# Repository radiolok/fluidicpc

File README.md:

# FluidicPC

Вычислительные устройства на элементах струйной логики: от моделей отдельных элементов и расчёта течения до синтеза схем и разводки плат.

## Проекты и инструменты

| Папка | Что внутри |
|---|---|
| [`calculator/`](calculator) | **Струйный калькулятор** — арт-объект на 852 элементах: распознаёт символ с матрицы трубочек 5 × 7, считает и показывает результат на семисегментных индикаторах. Модель, структурный и высокоуровневый Verilog, расчёты питания и конструктива |
| [`adder/`](adder) | 4-разрядный сумматор: Verilog, синтез в библиотеку струйных элементов (`fluidic.lib`), тестбенч |
| [`elements/`](elements) | 3D-модели элементов «Волга» (СТ41, СТ42, СТ43, СТ55, СТ56, СТ59, СТ60, СТ63 и др.) во FreeCAD |
| [`bench/`](bench) | расчёт течения в элементе СТ41 в OpenFOAM: подготовка сетки и запуск на кластере |
| [`sch/`](sch) | схемы и плата сумматора в KiCad |
| [`verilog2netlist/`](verilog2netlist) | конвертер синтезированного Verilog в netlist и плату KiCad |

## Струйный калькулятор

Ввод — трафарет на матрице трубочек и кнопка «Ввод». Операнды от 0 до 99, операции `+ − ×`. Схема разложена на 8 даёв по 150 элементов. Даи попарно собраны в 4 вертикальных блока, блоки стоят на объединительной плите с буферной полостью питания.

Подробнее — в [`calculator/README.md`](calculator/README.md).

## Лицензия

[LICENSE](LICENSE)

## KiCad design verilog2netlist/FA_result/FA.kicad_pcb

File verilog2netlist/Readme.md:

# verilog to netlist
Конвертирует verilog в netlist из которого можно сделать pcb в KiCad 6.

## Установка
Установка зависимостей
```:bash
pip install pipenv
pipenv shell
pipenv install
```
Зависимости: Python 3.8 или выше

## Использование

Входной верилог файл лежит в папке `verilog_inputs` по умолчанию это файл `adder_synth.v` из него будет сгенерирован netlist для заранее созданного Kicad проекта

В папке `FA` содержится пример пустого проекта Kicad со всеми библиотеками добавленными в проект. Эти библиотеки используются при создании netlist.

`FA_result` уже готовый что будет после работы скрипты. 

Конфигурационный файл config.py 

Для каждого модуля создаются свои правила по ключу в словаре. Каждый объект правил содержит ключи:
- `verilog_type` — имя элемента в верилог файле обязательно должны быть элементы для `input` и для `output` остальные например `NOT` опциональны если правила нет элемент в netlist не добавляется
- `kicad_schematic_lib` — имя кикад библиотеки схем так как его назвали при экспортировании в диалоге проекта Kicad 6 `Preferences → Manage Symbol Libraries... → **Project** Specific Libraries`
- `kicad_scheamtic_element` — Имя элемента как назван в библиотеке схем экспортированной выше
`kicad_footprint` — футпринт элемента в формате `{имя библиотеки}:{имя элемента}` в диалоге проекта Kicad 6 `Preferences → Manage Footprint Libraries... → Project Specific Libraries`
- `pins` — правила замены имен пинов из верилог файла в пины элемента Kicad. Пины в кикад могут быть названия как по `name` так и по `number`. В shematic элемента у пина могут быть указаны как `name` так и `number` оба параметра могут быть текстом. У footprint у пинов есть только `number`

Пример:

```
...
"FA": [{
    "verilog_type": "input",
    "kicad_schematic_lib": "FA",
    "kicad_schematic_element": "HOLE",
    "kicad_footprint": "FA:HOLE",
    "pins": {},
},
    {
    "verilog_type": "output",
        "kicad_schematic_lib": "FA",
        "kicad_schematic_element": "HOLE",
        "kicad_footprint": "FA:HOLE",
        "pins": {},
},{
    "verilog_type": "NOR",
        "kicad_schematic_lib": "FA",
        "kicad_schematic_element": "NOR",
        "kicad_footprint": "FA:NOR",
        "pins": {
            ".A": {
                "number": "4"
            },
            ".B": {
                "number": "5"
            },
            ".Y": {
                "number": "7"
            }},
},]
...
```
Элементы верилог файла
```
...
  input ci;
...
  output co;
...
  NOR _12_ (
    .A(_05_),
    .B(_06_),
    .Y(_08_)
  );
...
```

## Командная строка 
```
> python main.py
```

```
> python main.py --help
usage: main.py [-h] [-i [INPUT]] [-l [LIB]]
               [-o [OUTPUT]]

Convert verilog file to netlist

optional arguments:
  -h, --help            show this help
                        message and exit
  -i [INPUT], --input [INPUT]
                        Input verilog file.
                        default is verilog_in
                        puts/adder_synth.v
  -l [LIB], --lib [LIB]
                        Add kicad library
                        path. Multiple path
                        is allowed. default
                        is FA
  -o [OUTPUT], --output [OUTPUT]
                        Output folder.
                        default is
                        netlists_outputs
```
Необязательные параметры
- `-i` — имя входного верилог файла
- `-l` — путь до библиотеки Kicad 6 можно использовать не только проектную, но и глобальную библиотеку. Пути можно найти в документации по Kicad 6, можно добавить несколько путей для библиотек искать будет во всех.
- `-o` — имя папки куда попадут netlist от каждого модуля. Имя файла будет имя модуля с расширением `*.net`. Так же сюда попадет файл для библиотеки skidl оканчивающийся на `*_skidl.py`, который может сам сгенерировать netlist файл. При этом его удобно редактировать и в нем подробно указаны связи элементов. 

## Что делать с netlist

Можно создать новый проект добавив в него все библиотеки из исходного проект `*.kicad_sym`, папки `*.pretty` с файлами с расширением `*.kicad_mod`

В файле проект открыть `PCB editor`

Нажать `File → Import → Netlist` в Диалоге нажать `Update PCB` закрыть `Close`

К курсору прилипнут все элементы из netlist расположить их в удобном месте. Все соединенные пины будут соединены прямой линией

Расставить элементы так как будет удобно.

После этого можно будет сделать автотрассировку

## Автотрассировка

Скачать и установить LayoutEditor https://layouteditor.com/download если нет java то её тоже установить https://www.java.com/

Нажать в Kicad PCD Editor `File → Export → Spectra DSN...` сохранить.

В установленном приложении LayoutEditor найти файл `freeRouting.jar` в Windows в папке программ `LayoutEditor\bin\freeRouting.jar`

Запустить в диалоге выбрать `*.dsn` файл созданные ранее. 

В открывшемся приложении выбрать `Routing → Autorouting` Когда процесс завершится нажать `File → Export → Export Spectra Session File` Файл сохранится в той же папке и с тем же названием только расширение будет `*.ses` на вопрос нажать `Yes`

В `PCB Editor` из Kicad открыв тот же файл куда импортировался netlist нажать `File → Import → Spectra Session...` выбрать созданный `*.ses` файл. Все элементы соединятся проводниками.

Теперь можно выбрать один или несколько выходов и нажать апостроф "`" пути соединений будут подсвечены.

Удалить путь чтобы разметить заново `Edit → Global Deletions...` выбрать `Tracks & vias` → `OK` → `Yes`. Теперь можно переставить элементы и сделать автотрассировку заново.

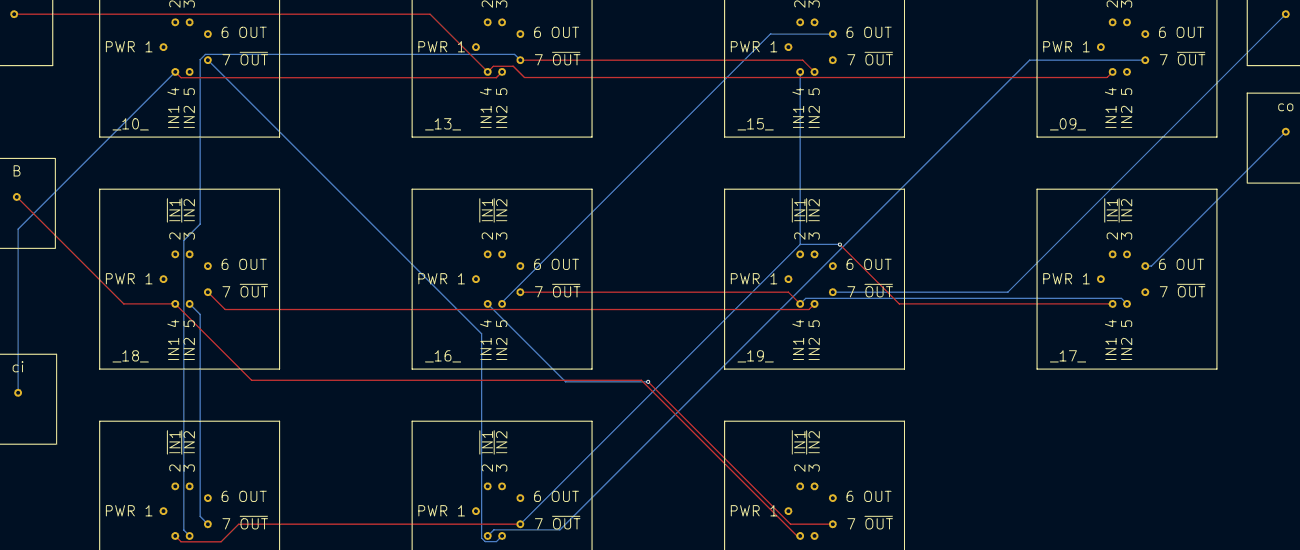
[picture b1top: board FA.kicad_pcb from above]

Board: 2 copper layers, 16 parts (0 on the bottom side), 14 nets.

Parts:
A: INPUT
B: INPUT
_09_, _10_, _11_: NOT; NOR
_12_, _13_, _14_, _16_, _18_, _19_: NOR
_15_, _17_: OR; NOR
ci: INPUT
co: OUTPUT
out: OUTPUT

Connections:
A: A.1, _09_.4, _13_.4
B: B.1, _11_.4, _18_.4
_00_: _13_.7, _14_.5, _15_.5
_01_: _14_.7, _18_.5
_02_: _15_.6, _16_.5
_03_: _16_.7, _17_.5, _19_.4
_04_: _18_.7, _19_.5
_05_: _09_.7, _12_.4
_06_: _10_.7, _12_.5
_07_: _11_.7, _16_.4
_08_: _12_.7, _14_.4, _15_.4, _17_.4
ci: _10_.4, _13_.5, ci.1
co: _17_.6, co.1
out: _19_.7, out.1

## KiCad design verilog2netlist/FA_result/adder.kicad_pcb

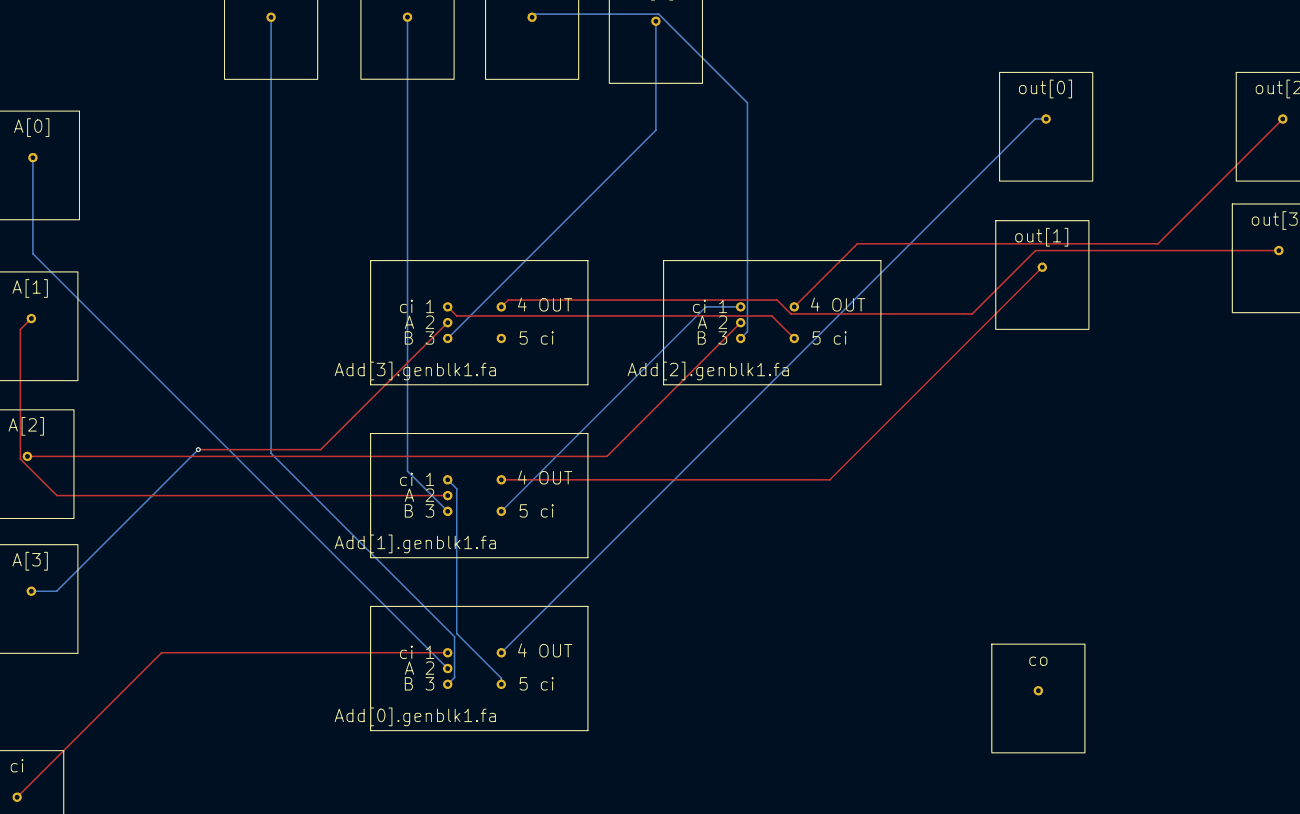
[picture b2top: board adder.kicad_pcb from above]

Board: 2 copper layers, 18 parts (0 on the bottom side), 16 nets.

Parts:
A[0], A[1], A[2], A[3]: INPUT
Add[0].genblk1.fa, Add[1].genblk1.fa, Add[2].genblk1.fa, Add[3].genblk1.fa: FA; genblk1.fa
B[0], B[1], B[2], B[3]: INPUT
ci: INPUT
co: OUTPUT
out[0], out[1], out[2], out[3]: OUTPUT

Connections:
A[0]: A[0].1, Add[0].genblk1.fa.2
A[1]: A[1].1, Add[1].genblk1.fa.2
A[2]: A[2].1, Add[2].genblk1.fa.2
A[3]: A[3].1, Add[3].genblk1.fa.2
Add[0].c_out: Add[0].genblk1.fa.5, Add[1].genblk1.fa.1
Add[1].c_out: Add[1].genblk1.fa.5, Add[2].genblk1.fa.1
Add[2].c_out: Add[2].genblk1.fa.5, Add[3].genblk1.fa.1
B[0]: Add[0].genblk1.fa.3, B[0].1
B[1]: Add[1].genblk1.fa.3, B[1].1
B[2]: Add[2].genblk1.fa.3, B[2].1
B[3]: Add[3].genblk1.fa.3, B[3].1
ci: Add[0].genblk1.fa.1, ci.1
out[0]: Add[0].genblk1.fa.4, out[0].1
out[1]: Add[1].genblk1.fa.4, out[1].1
out[2]: Add[2].genblk1.fa.4, out[2].1
out[3]: Add[3].genblk1.fa.4, out[3].1

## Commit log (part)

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2022-07-23 Add initial fibonachi code
2022-07-23 fix spaces
2022-07-23 fix fluidic.lib
2022-07-23 Just adder
2022-07-24 Rewrote to adder
2022-07-27 add 50u bench
2022-07-27 Add readme file
2022-07-27 fix hostfile
2022-07-27 renamed folder
2022-07-27 add kicad sch
2022-07-29 add openfoam instructions
2022-07-30 petsc
2022-07-30 Docker
2022-07-30 for Docker
2022-07-31 some updates
2022-07-31 Add petscfoam step. now openfoam installed incorrectly
2022-07-31 Fix petscfoam
2022-08-06 Add ci co
2022-08-10 Rewriten to use FA
2022-08-10 Update code to fix sim issues
2022-08-10 Manual import of 4bit adder to kicad
2022-10-22 add FreeCAD elements
2022-12-01 Added verilog2Netlist converter
    This new code conver yosys output to kiCad netlist
    Idea - mine,
    Author - https://habr.com/ru/users/Pechkin1007/
2023-02-11 Added verilog2Netlist converter
    This new code conver yosys output to kiCad netlist
2024-11-05 Add VOLGA elements 3d models
